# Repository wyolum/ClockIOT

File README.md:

# ClockIOT
Word Clock

/kicad will be the latest HW version.
Earlier versions get sequentially numbered _v0, _v1 etc.

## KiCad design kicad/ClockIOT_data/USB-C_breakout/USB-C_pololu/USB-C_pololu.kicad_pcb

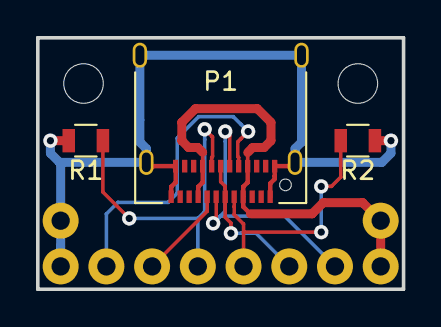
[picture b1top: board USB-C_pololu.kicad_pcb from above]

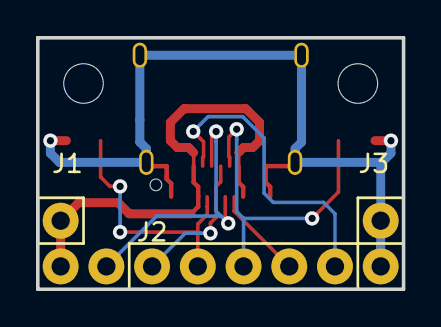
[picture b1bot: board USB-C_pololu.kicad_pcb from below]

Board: 2 copper layers, 20.3 x 14.0 mm, 6 parts (3 on the bottom side), 8 nets.

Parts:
J1: VBUS; Socket_Strip_Straight_1x02
J2: IO; Socket_Strip_Straight_1x06
J3: GND; Socket_Strip_Straight_1x02
P1: USB_C_Receptacle; USB_C_Receptacle_Amphenol_12401610E4-2A
R1, R2: 5k11; R_0805

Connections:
/CC1: J2.3, P1.A5, R2.1
/CC2: J2.4, P1.B5, R1.1
/D+: J2.2, P1.A6, P1.B6
/D-: J2.1, P1.A7, P1.B7
/SBU1: J2.5, P1.A8
/SBU2: J2.6, P1.B8
/VBUS: J1.1, J1.2, P1.A4, P1.A9, P1.B4, P1.B9
GND: J3.1, J3.2, P1.A1, P1.A12, P1.B1, P1.B12, P1.S1, R1.2, R2.2

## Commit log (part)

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2018-03-22 initial commit (copyied and renamed from KlokTHREEjr
2018-03-25 renamed clock.h to prevent conflicts
2018-04-08 transferred Kicad files from old repo
2018-04-10 cleanup
2018-06-02 _v0 is prototype, _v1 has USB/Batt on top side. All parts on top side = WIP
2018-06-03 Problem incorporating Time.h
2018-06-03 added FastLED lib
2018-06-03 added WiFiManager lib
2018-06-03 added eeprom anything:
2018-06-03 added bunch of libs... thanks Kevin for finding themgit add libraries/NTPClient/*
2018-06-03 use local time lib
2018-06-03 fix up various references
2018-06-03 changed years to year
2018-06-03 moved all parts to top layer except buttons
2018-06-03 added doomsday_clock
2018-06-04 layout WIP
2018-06-04 ClockIOT new version layout complete. All parts on top layer. Gerbers ready
2018-06-05 Layout checked. Gerbers ready
2018-06-07 fix data and clock pins for Clockiot
2018-06-10 Layoadded 'rev 2' to silk legend
2018-06-11 minor silk legend corrections
2018-06-12 prettified layout
2018-08-18 start of ClockIOT_MFGTest
2018-08-18 readme edit
2018-08-18 reduce default brightmess in ClockIOT_MFGTest
2018-08-18 bundle for MFG_Test
2018-09-03 mqtt, 3 displays and added initial interface with node red
2018-09-03 minor updates
2018-09-04 added http lookup of timezone
2018-09-06 got eeprom working by adding call to EEPROM.begin(1024)
2018-09-09 added RTCLib
2018-09-23 First ClockIOT.ino upload from seeed protos
2018-09-24 add ifdefs to allow Dulles Klok and ClockIOT
2018-09-24 added WebSockets interface
2018-09-24 added WebSockets python interface
2018-09-26 started barebones clock wo web stuff
2018-09-26 added ntp clock to barebones
2018-09-27 #defined out web stuff in BareBones
2018-09-29 added HW Torture Test
2018-10-03 Stand-alone mode now supported
2018-10-04 added mqtt_ip address setting from websocket
2018-10-05 checkin
2018-10-05 fixed linix incompatiblility
2018-10-06 added timezone changes to mqtt interface
2018-10-06 BoM update, Buttons
2018-10-06 added updates to request timezone only sunday's between 3 and 4
2018-10-07 added Mac Address to mqtt id
2018-10-07 reduced default brightnes to 8
2018-10-10 Now pulling local IPs from wyolum.com
2018-10-11 updated _GUI
2018-10-14 Delete 68747470733a2f2f77796f6c756d2e636f6d2f646f63732f436c6f636b494f542f496d616765732f53637265656e25323053686f74253230323031382d31302d3037253230617425323031322e30382e3335253230504d2e706e67.png
    filename too long
2018-10-14 renamed images
2018-10-17 adding USB-C breakout to PCB
2018-10-18 added USB-C breakout footprint to PCB
2018-10-19 Added USB-C breakout board addon to PCB
2018-10-19 rev 4 gerbers
2018-10-21 added pullup for RST and pulldown for SUSPEND CP2102
2018-10-27 minor updates and bug fix to ClockIOT_gui
2018-10-27 added control from Serial interface
2018-10-27 added solid color display that grabs RGB from config
2018-10-28 added color changing option
2018-10-28 added custom color to TheMatrix
2018-10-28 added low pwr mode to prevent brown outs when programming. hold enter while booting to go to low pwr mode
2018-10-30 new rev 3 Gerbers, PDF, renders, BoM
2018-11-03 added get_displays message to web sockets
2018-11-03 added colorwheel code
2018-11-03 added dispay_idx to json string
2018-11-03 added Fire Noise
2018-11-03 Added basic web ui
2018-11-04 Added timezone picker using https://github.com/kevalbhatt/timezone-picker
2018-11-04 It finally works
2018-11-04 Changed timezone map to use imagemap and connected it to api
2018-11-10 Fixed mixed content error in webui
2018-11-10 added clockiot/timezone_offset//IP command to revert to using IP address for timezone offset
2018-11-11 Fixed timezone picker bugs
2018-11-12 bug fix
2018-11-12 fixed use_ip_timezone automatic settings
2018-11-12 Fixed several bugs in timezone picker and added option to have clock find timezone
2018-11-12 Fixed mistake in last commit
2018-11-12 OK, fixed one last typo, now it works
2018-11-14 rev 4, added 3 pin headers for CLK/DAT/GND for building bigger matrices
2018-11-16 added bitmap for splash screen
2018-11-17 Added automatic fix for SecurityError from browser
2018-11-18 added faceplate code and Simulate.py for creating language h files
2018-11-19 added from __future__ import print_function to some files
2018-12-17 Fixed wrong case include preventing compile on linux
2018-12-17 Added language selector and fixed default display choice
    - Added a basic language list and selector
    - Fixed a bug where the currently selected display would not be the
    default selection of the display list
2018-12-17 fixed faceplate_idx message
2019-01-01 added image
2019-01-01 moved image
2019-01-08 commented out inthisreality import
2019-02-02 Fixed faceplate list from api
    After inthisreality stuff, the N_FACEPLATE variable was too large, which
    caused the websocket interface to return invalid JSON when asked for the
    list of faceplates. I also commented a inthisreality thing that was
    causing errors.
2019-02-02 added color wheel code and image
2019-02-18 Improved Display and Language selection
    - Removed "Set Display" button, now it changes as you change the
    dropdown selection
    - Changed language list to remove all faceplates but the latest version,
    unless developerMode is true
    - Added settings object, currently only read from
    - TODO:Add settings panel
2019-03-10 Added loading wheel and improved css
    I changed the select styling to make it consistent across all browsers,
    and also modified the clock selection so that the ui only shows that
    until you select a clock, at which point it shows a loading wheel until
    the display list is populated and it shows all the controls
2019-03-14 Initial ColorPicker working Still a bug about the color chosen though
2019-05-06 Base line for UI
2019-08-28 http client example for new offset api
2019-08-28 added esp32 version of WyoBean
2019-08-28 working on WyoBean32 http bug
2019-09-08 Assembly CAD and BoM
2019-09-08 fixed DST bug
2019-09-09 Seeed production files, Assembly CAD and BoM
2019-09-09 ClockIoT new back plate
2019-09-09 new CAD renders
2019-09-12 added missing h files
2019-09-16 ClockIoT faceplate PDF added
2019-11-08 Fixed set_timezone_from_ip bug that used Sunday==0 (wrong) to Sunday==1 (right).
2019-11-09 reverted version of wifi manager to version 14
2019-11-29 updated ClockIoT BoM
2019-11-30 added stand from Nick
2019-12-05 ClockIOT.ino is first production version, debugging button crashes
2019-12-06 minimal changes to get to compile (strange that production code did not compilegit reset --hard HEAD WTF?)
2019-12-06 Fixed resetting bug caused by accessing ds3231 and/or ntp before setup was complete
2019-12-07 Created Flashing doc
2019-12-07 created small python app to control clock. fixed use_ntp bug
2019-12-07 update websockets library
2019-12-07 disabled buttons on ClockIOT commander.py
2019-12-09 cleaned up folder structure
2019-12-12 Fixed get_time.cpp to fall back to realtime clock when NTP clock is not initialized
2019-12-12 minor update for testing
2019-12-14 Fixed timezone picker errors Resized timezone map image to fit better
2019-12-15 Added source on github link to header Added "Web Design by Evil Genius Labs" link to header
2019-12-15 Exit changeClock after http redirect.
2019-12-16 added ClockIOT.stl stand
2019-12-17 updated backplate SVG and PDF
2019-12-18 added cord bottom and cord top versions of backplate
2019-12-20 Adds ClockIOT mockup for testing and debugging.
    This commit adds a mockup that mimics a real clock and can display it's
    own internal state. It's specifically made for when there's a bug that
    needs to be fixed now, but you left your clock at home. See the README for more info.
2019-12-21 Updated plugin to remove security warning.
2019-12-25 added backup url (direct to ipapi) in case wyolum fails
2019-12-26 added User guide from Nick
2019-12-27 adding 2-board clock Chromogram
2019-12-27 First draft of 2-board clock 'Chromogram2'
2019-12-27 fixed Chromogram to display the right time
2019-12-29 Fixed Chromogram2 MatrixMap
2019-12-29 added english2_v1.h
2019-12-29 ifdefed API key
2019-12-30 integreated Kevin's .h file patch
2019-12-30 added MatrixMap.*
2020-01-02 added Nick's Chromogram faceplate and backplate
2020-01-02 added Nick's chomorgram stand
2020-01-02 added read wtf
2020-01-06 added Armenian_v1.wtf
2020-01-26 KiCad v5 - new expansion headers, new qwiic headers, wider breakoff tabs
2020-01-27 v5 BOM and new back plate design
2020-02-05 updated backplate and BoM
2020-03-14 Bump acorn from 7.1.0 to 7.1.1 in /mockup
    Bumps [acorn](https://github.com/acornjs/acorn) from 7.1.0 to 7.1.1.
    - [Release notes](https://github.com/acornjs/acorn/releases)
    - [Commits](https://github.com/acornjs/acorn/compare/7.1.0...7.1.1)
2020-07-19 Bump lodash from 4.17.15 to 4.17.19 in /mockup
    Bumps [lodash](https://github.com/lodash/lodash) from 4.17.15 to 4.17.19.
    - [Release notes](https://github.com/lodash/lodash/releases)
    - [Commits](https://github.com/lodash/lodash/compare/4.17.15...4.17.19)
2021-05-10 Bump lodash from 4.17.15 to 4.17.21 in /mockup
    Bumps [lodash](https://github.com/lodash/lodash) from 4.17.15 to 4.17.21.
    - [Release notes](https://github.com/lodash/lodash/releases)
    - [Commits](https://github.com/lodash/lodash/compare/4.17.15...4.17.21)
2021-08-04 Bump tar from 4.4.13 to 4.4.15 in /mockup
    Bumps [tar](https://github.com/npm/node-tar) from 4.4.13 to 4.4.15.
    - [Release notes](https://github.com/npm/node-tar/releases)
    - [Changelog](https://github.com/npm/node-tar/blob/main/CHANGELOG.md)
    - [Commits](https://github.com/npm/node-tar/compare/v4.4.13...v4.4.15)
    ---
    updated-dependencies:
2021-08-11 Bump path-parse from 1.0.6 to 1.0.7 in /mockup
    Bumps [path-parse](https://github.com/jbgutierrez/path-parse) from 1.0.6 to 1.0.7.
    - [Release notes](https://github.com/jbgutierrez/path-parse/releases)
    - [Commits](https://github.com/jbgutierrez/path-parse/commits/v1.0.7)
    ---
    updated-dependencies:
    - dependency-name: path-parse
2021-09-02 Bump tar from 4.4.13 to 4.4.19 in /mockup
    Bumps [tar](https://github.com/npm/node-tar) from 4.4.13 to 4.4.19.
    - [Release notes](https://github.com/npm/node-tar/releases)
    - [Changelog](https://github.com/npm/node-tar/blob/main/CHANGELOG.md)
    - [Commits](https://github.com/npm/node-tar/compare/v4.4.13...v4.4.19)
    ---
    updated-dependencies:
2022-02-12 Bump ajv from 6.10.2 to 6.12.6 in /mockup
    Bumps [ajv](https://github.com/ajv-validator/ajv) from 6.10.2 to 6.12.6.
    - [Release notes](https://github.com/ajv-validator/ajv/releases)
    - [Commits](https://github.com/ajv-validator/ajv/compare/v6.10.2...v6.12.6)
    ---
    updated-dependencies:
    - dependency-name: ajv
2022-07-15 Bump svelte from 3.15.0 to 3.49.0 in /mockup
    Bumps [svelte](https://github.com/sveltejs/svelte) from 3.15.0 to 3.49.0.
    - [Release notes](https://github.com/sveltejs/svelte/releases)
    - [Changelog](https://github.com/sveltejs/svelte/blob/master/CHANGELOG.md)
    - [Commits](https://github.com/sveltejs/svelte/compare/v3.15.0...v3.49.0)
    ---
    updated-dependencies:
2022-07-20 Bump terser from 4.4.3 to 4.8.1 in /mockup
    Bumps [terser](https://github.com/terser/terser) from 4.4.3 to 4.8.1.
    - [Release notes](https://github.com/terser/terser/releases)
    - [Changelog](https://github.com/terser/terser/blob/master/CHANGELOG.md)
    - [Commits](https://github.com/terser/terser/commits)
    ---
    updated-dependencies:
